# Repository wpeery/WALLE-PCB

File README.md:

# WALLE-PCB
The 2nd Gen PCB for the WALLE Capstone 2018

This PCB code base uses EAGLE PCB Design from Autodesk. These files can only be edited using their software. You can make an account and register for EAGLE via the Autodesk account. Here's the link: https://www.autodesk.com/education/free-software/eagle

Students get to use the premium edition for **FREE**

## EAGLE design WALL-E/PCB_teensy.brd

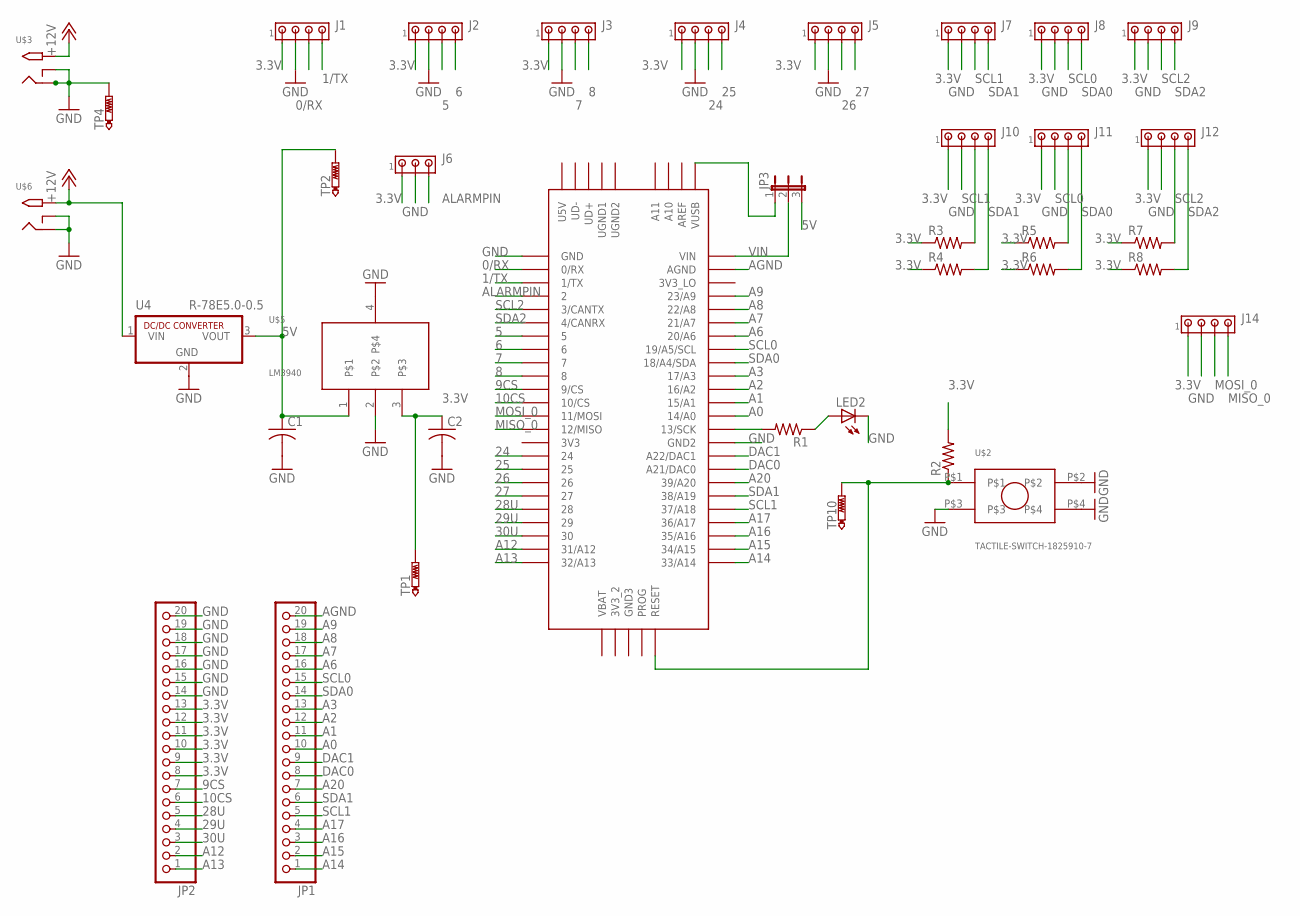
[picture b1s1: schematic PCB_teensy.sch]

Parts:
C1, C2: C-USC0805; C0805
J1, J2, J3, J4, J5, J7, J8, J9, J10, J11, J12, J14: MTA04-100; 10X04MTA
J6: MTA03-100; 10X03MTA
JP1, JP2: PINHD-1X20; 1X20
JP3: JP2W
LED2: LEDCHIP-LED0805; CHIP-LED0805
R1, R2, R3, R4, R5, R6, R7, R8: R-US_R0805; R0805
TP1, TP2, TP4, TP10: PTR1B2,54; B2,54
U4: R-78E5.0-0.5; SIP3
U$1: TEENSY_3.5/3.6
U$2: TACTILE-SWITCH-1825910-7; 1825910-7
U$3, U$6: 2.1MMJACKTHM; PJ-102A
U$5: LM3940; SOT223

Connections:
0/RX: J1.3, U$1.0/RX
1/TX: J1.4, U$1.1/TX
3.3V: C2.1, J1.1, J2.1, J3.1, J4.1, J5.1, J6.1, J7.1, J8.1, J9.1, J10.1, J11.1, J12.1, J14.1, JP2.8, JP2.9, JP2.10, JP2.11, JP2.12, JP2.13, R2.2, R3.1, R4.1, R5.1, R6.1, R7.1, R8.1, TP1.TP, U$5.3
5: J2.3, U$1.5
5V: C1.1, JP3.3, TP2.TP, U4.3 (VOUT), U$5.1
6: J2.4, U$1.6
7: J3.3, U$1.7
8: J3.4, U$1.8
9CS: JP2.7, U$1.9/CS
10CS: JP2.6, U$1.10/CS
24: J4.3, U$1.24
25: J4.4, U$1.25
26: J5.3, U$1.26
27: J5.4, U$1.27
28U: JP2.5, U$1.28
29U: JP2.4, U$1.29
30U: JP2.3, U$1.30
+12V: U4.1 (VIN), U$3.TIP, U$6.TIP
A0: JP1.10, U$1.14/A0
A1: JP1.11, U$1.15/A1
A2: JP1.12, U$1.16/A2
A3: JP1.13, U$1.17/A3
A6: JP1.16, U$1.20/A6
A7: JP1.17, U$1.21/A7
A8: JP1.18, U$1.22/A8
A9: JP1.19, U$1.23/A9
A12: JP2.2, U$1.31/A12
A13: JP2.1, U$1.32/A13
A14: JP1.1, U$1.33/A14
A15: JP1.2, U$1.34/A15
A16: JP1.3, U$1.35/A16
A17: JP1.4, U$1.36/A17
A20: JP1.7, U$1.39/A20
AGND: JP1.20, U$1.AGND
ALARMPIN: J6.3, U$1.2
DAC0: JP1.8, U$1.21/DAC0 (A21/DAC0)
DAC1: JP1.9, U$1.A22/DAC1
GND: C1.2, C2.2, J1.2, J2.2, J3.2, J4.2, J5.2, J6.2, J7.2, J8.2, J9.2, J10.2, J11.2, J12.2, J14.2, JP2.14, JP2.15, JP2.16, JP2.17, JP2.18, JP2.19, JP2.20, LED2.C, TP4.TP, U4.2 (GND), U$1.GND, U$1.GND2, U$2.P$2, U$2.P$3, U$2.P$4, U$3.RING, U$3.RING_SW, U$5.2, U$5.4, U$6.RING, U$6.RING_SW
MISO_0: J14.4, U$1.12/MISO
MOSI_0: J14.3, U$1.11/MOSI
unnamed: JP3.1, U$1.VUSB
unnamed: R2.1, TP10.TP, U$1.RESET, U$2.P$1
unnamed: R1.2, U$1.13/SCK
unnamed: LED2.A, R1.1
SCL0: J8.3, J11.3, JP1.15, R5.2, U$1.19/A5/SCL
SCL1: J7.3, J10.3, JP1.5, R3.2, U$1.37/A18
SCL2: J9.3, J12.3, R7.2, U$1.3/CANTX
SDA0: J8.4, J11.4, JP1.14, R6.2, U$1.18/A4/SDA
SDA1: J7.4, J10.4, JP1.6, R4.2, U$1.38/A19
SDA2: J9.4, J12.4, R8.2, U$1.4/CANRX
VIN: JP3.2, U$1.VIN

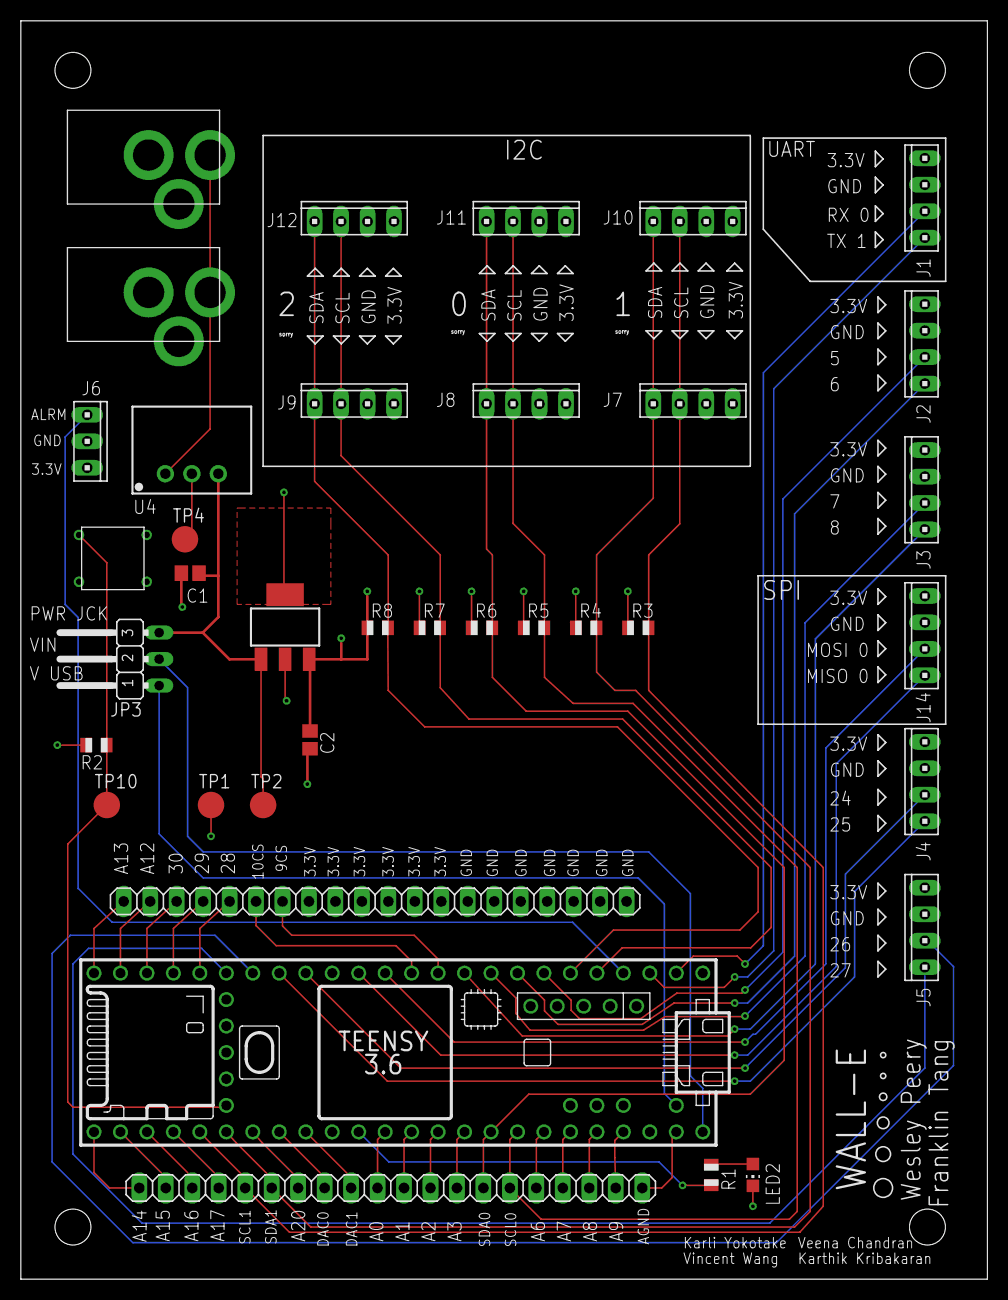
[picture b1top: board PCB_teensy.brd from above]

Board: 4 copper layers, 92.8 x 120.8 mm, 37 parts (0 on the bottom side), 51 nets.

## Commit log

2018-03-12 Adds project file
    initial commit
2018-03-18 updated schematic
2018-03-19 started on the layout
2018-03-19 Moved the layout to optimal positions.
2018-04-02 added some pull up resistor and added 5v power to teensy with a jumper
2018-04-04 Rewired the JP1 pins to be physically closer to the teensy board.
2018-04-04 Rewired the pins for JP2 to make the pins be physically closer to the teensy.
2018-04-04 Routed all the header pins closest to Teensy and resistors.
2018-04-05 Finished wiring the layers besides the tactile switch.
2018-04-05 finished routing
2018-04-05 jk now routing is finished
2018-04-05 resized the board
2018-04-05 Added silkscreen to the teensy header pins.
2018-04-05 Added silkscreen to alarm pin and shifted the components to the top right for more silkscreen real estate.
2018-04-05 added silkscreen to i2c headers
2018-04-07 Added power and ground silkscreen to the other J headers.
2018-04-07 Finished labeling the silkscreen for everything.
2018-04-07 Added the last silkscreen to UART J header and a heatsink to the voltage regulator.
2018-04-07 Spend 3 hours on logo but ended up typing it.#legit
2018-04-07 removed extra top layer polygon and moved dimension to dimension layer. Also spaced out barrel jacks slightly
2018-04-09 removed some test pins
2018-04-09 removed 3.3v power routes, now components connect to the power plane
2018-04-09 cleaned up each layer
2018-04-09 added tp1 for 3.3V
2018-04-10 combined top and bottom layers into one top layer. Also added power and ground to middle planes
2018-04-10 moved light blue layer and light red layer into one light red layer
2018-04-10 moved light red layer to bottom layer. Routing should be done
2018-04-13 Added mounting holes for 4-40 screws and dimensions for drilling.
2018-04-13 moved dimension at the top
2018-04-13 removed dimensions
2018-04-13 added images in separate directory
2018-04-13 remove old pictures
2018-04-13 removed a bunch of unneeded vias
2018-04-13 removed a couple more vias
2018-04-13 adds image
2018-04-15 Generated the Gerber files using the Sunstone Circuits CAM job.
2018-04-16 Regenerated the Gerber files based on Full name.
2018-04-16 beefed up power wires that go to power plane
2018-04-16 removed some unneeded bypass caps
2018-04-16 generated new gerber and drill files
2018-05-18 fixes power jack and tactile switch
